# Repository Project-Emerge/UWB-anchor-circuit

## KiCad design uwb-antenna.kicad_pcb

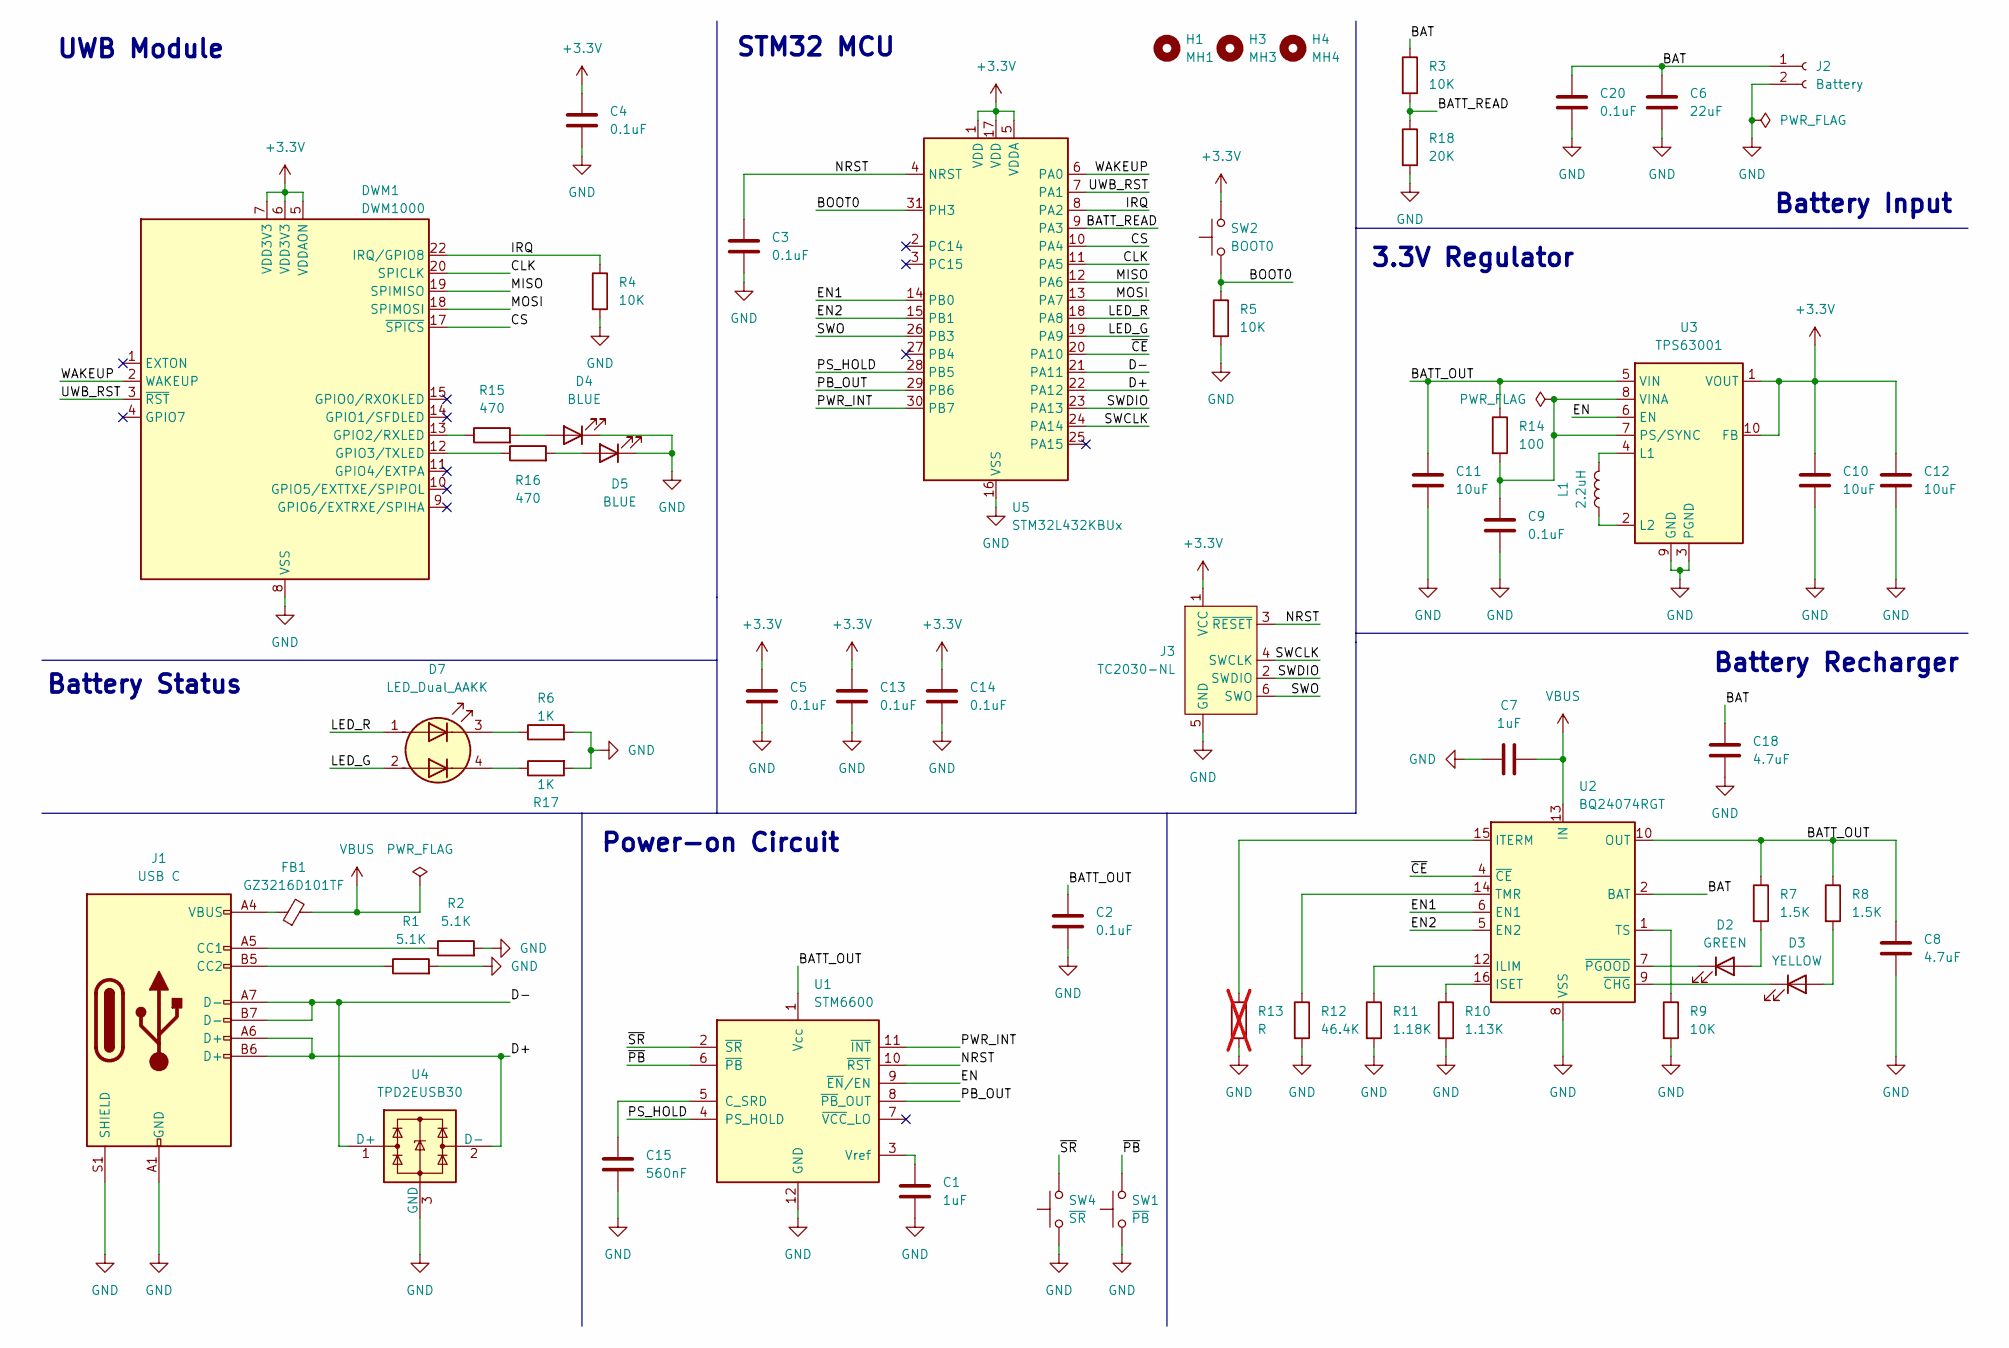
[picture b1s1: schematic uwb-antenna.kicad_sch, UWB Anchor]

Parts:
C1: 1uF; C_0402_1005Metric; LCSC C14445
C2, C3, C4, C5, C13, C14: 0.1uF; C_0402_1005Metric; LCSC C307331
C6: 22uF; C_1210_3225Metric; LCSC C5341638
C7: 1uF; C_0805_2012Metric; LCSC C91185
C8, C18: 4.7uF; C_0805_2012Metric; LCSC C1779
C9: 0.1uF; C_0201_0603Metric; LCSC C14663
C10, C11, C12: 10uF; C_0603_1608Metric; LCSC C48579272
C15: 560nF; C_0402_1005Metric; LCSC C162174
C20: 0.1uF; C_0805_2012Metric; LCSC C49678
D2: GREEN; LED_0402_1005Metric; LCSC C130723
D3: YELLOW; LED_0402_1005Metric; LCSC C136118
D4, D5: BLUE; LED_0402_1005Metric; LCSC C130724
D7: LED_Dual_AAKK; LED_LiteOn_LTST-C295K_1.6x0.8mm; LCSC C284909
DWM1: DWM1000
FB1: GZ3216D101TF; L_1206_3216Metric; LCSC C369799
H1: MH1; MountingHole_3.2mm_M3_Pad
H3: MH3; MountingHole_3.2mm_M3_Pad
H4: MH4; MountingHole_3.2mm_M3_Pad
J1: USB C; USB_C_Receptacle_XKB_U262-16XN-4BVC11; LCSC C319148
J2: Battery; JST_PH_S2B-PH-SM4-TB_1x02-1MP_P2.00mm_Horizontal; LCSC C295747
J3: TC2030-NL; Tag-Connect_TC2030-IDC-NL_2x03_P1.27mm_Vertical
L1: 2.2uH; L_Coilcraft_LPS3010; LCSC C5350399
R1, R2: 5.1K; R_0402_1005Metric; LCSC C25905
R3, R4, R5, R9: 10K; R_0402_1005Metric; LCSC C25744
R6, R17: 1K; R_0402_1005Metric; LCSC C11702
R7, R8: 1.5K; R_0402_1005Metric; LCSC C25867
R10: 1.13K; R_0402_1005Metric; LCSC C67014
R11: 1.18K; R_0402_1005Metric; LCSC C270651
R12: 46.4K; R_0402_1005Metric; LCSC C52378
R13: R; R_0402_1005Metric; not fitted
R14: 100; R_0201_0603Metric; LCSC C22775
R15, R16: 470; R_0402_1005Metric; LCSC C25117
R18: 20K; R_0402_1005Metric; LCSC C25765
SW1: ~{PB}; SW_SPST_B3U-1000P; LCSC C231329
SW2: BOOT0; SW_SPST_B3U-1000P; LCSC C231329
SW4: ~{SR}; SW_SPST_B3U-1000P; LCSC C231329
U1: STM6600; TDFN-12_2x3mm_P0.5mm; LCSC C443976
U2: BQ24074RGT; VQFN-16-1EP_3x3mm_P0.5mm_EP1.6x1.6mm; LCSC1 C54313
U3: TPS63001; Texas_DRC0010J_ThermalVias; LCSC C28060
U4: TPD2EUSB30; Texas_DRT-3; LCSC C97502
U5: STM32L432KBUx; QFN-32-1EP_5x5mm_P0.5mm_EP3.45x3.45mm; LCSC C94784

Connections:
+3.3V: C4.1, C5.1, C10.1, C12.1, C13.1, C14.1, DWM1.5 (VDDAON), DWM1.6 (VDD3V3), DWM1.7 (VDD3V3), J3.1 (VCC), SW2.2, U3.1 (VOUT), U3.10 (FB), U5.1 (VDD), U5.5 (VDDA), U5.17 (VDD)
/BAT: C6.1, C18.1, C20.1, J2.1, R3.1, U2.2 (BAT), U2.3 (BAT)
/BATT_OUT: C2.1, C8.1, C11.1, R7.1, R8.1, R14.1, U1.1 (Vcc), U2.10 (OUT), U2.11 (OUT), U3.5 (VIN)
/BATT_READ: R3.2, R18.1, U5.9 (PA3)
/BOOT0: R5.1, SW2.1, U5.31 (PH3)
/CLK: DWM1.20 (SPICLK), U5.11 (PA5)
/CS: DWM1.17 (~SPICS), U5.10 (PA4)
/D+: J1.A6 (D+), J1.B6 (D+), U4.2 (D-), U5.22 (PA12)
/D-: J1.A7 (D-), J1.B7 (D-), U4.1 (D+), U5.21 (PA11)
/EN: U1.9 (~EN/EN), U3.6 (EN)
/EN1: U2.6 (EN1), U5.14 (PB0)
/EN2: U2.5 (EN2), U5.15 (PB1)
/IRQ: DWM1.22 (IRQ/GPIO8), R4.1, U5.8 (PA2)
/LED_G: D7.2 (A2), U5.19 (PA9)
/LED_R: D7.1 (A1), U5.18 (PA8)
/MISO: DWM1.19 (SPIMISO), U5.12 (PA6)
/MOSI: DWM1.18 (SPIMOSI), U5.13 (PA7)
/NRST: C3.1, J3.3 (~RESET), U1.10 (~RST), U5.4 (NRST)
/PB_OUT: U1.8 (~PB_OUT), U5.29 (PB6)
/PS_HOLD: U1.4 (PS_HOLD), U5.28 (PB5)
/PWR_INT: U1.11 (~INT), U5.30 (PB7)
/SWCLK: J3.4 (SWCLK), U5.24 (PA14)
/SWDIO: J3.2 (SWDIO), U5.23 (PA13)
/SWO: J3.6 (SWO), U5.26 (PB3)
/UWB_RST: DWM1.3 (~RST), U5.7 (PA1)
/WAKEUP: DWM1.2 (WAKEUP), U5.6 (PA0)
/~CE: U2.4 (~CE), U5.20 (PA10)
/~PB: SW1.2, U1.6 (~PB)
/~SR: SW4.2, U1.2 (~SR)
GND: C1.2, C2.2, C3.2, C4.2, C5.2, C6.2, C7.2, C8.2, C9.2, C10.2, C11.2, C12.2, C13.2, C14.2, C15.2, C18.2, C20.2, D4.1 (K), D5.1 (K), DWM1.8 (VSS), DWM1.16 (VSS), DWM1.21 (VSS), DWM1.23 (VSS), DWM1.24 (VSS), J1.A1 (GND), J1.A12 (GND), J1.B1 (GND), J1.B12 (GND), J1.S1 (SHIELD), J2.2, J3.5 (GND), R1.2, R2.2, R4.2, R5.2, R6.2, R9.2, R10.2, R11.2, R12.2, R13.2, R17.2, R18.2, SW1.1, SW4.1, U1.12 (GND), U2.8 (VSS), U2.17 (VSS), U3.3 (PGND), U3.9 (GND), U3.11 (PGND), U4.3 (GND), U5.16 (VSS), U5.32 (VSS), U5.33 (VSS)
unnamed: D2.2 (A), R7.2
unnamed: D2.1 (K), U2.7 (~PGOOD)
unnamed: D3.2 (A), R8.2
unnamed: D3.1 (K), U2.9 (~CHG)
unnamed: D4.2 (A), R15.2
unnamed: D5.2 (A), R16.2
unnamed: D7.3 (K1), R6.1
unnamed: D7.4 (K2), R17.1
unnamed: DWM1.13 (GPIO2/RXLED), R15.1
unnamed: DWM1.12 (GPIO3/TXLED), R16.1
unnamed: FB1.1, J1.A4 (VBUS), J1.A9 (VBUS), J1.B4 (VBUS), J1.B9 (VBUS)
unnamed: J1.A5 (CC1), R2.1
unnamed: J1.B5 (CC2), R1.1
unnamed: C15.1, U1.5 (C_SRD)
unnamed: C1.1, U1.3 (Vref)
unnamed: R11.1, U2.12 (ILIM)
unnamed: R10.1, U2.16 (ISET)
unnamed: R13.1, U2.15 (ITERM)
unnamed: R12.1, U2.14 (TMR)
unnamed: R9.1, U2.1 (TS)
unnamed: L1.2, U3.4 (L1)
unnamed: L1.1, U3.2 (L2)
unnamed: C9.1, R14.2, U3.7 (PS/SYNC), U3.8 (VINA)
VBUS: C7.1, FB1.2, U2.13 (IN)

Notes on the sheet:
3.3V Regulator
Battery Recharger
Power-on Circuit
STM32 MCU
Battery Status
Battery Input
UWB Module

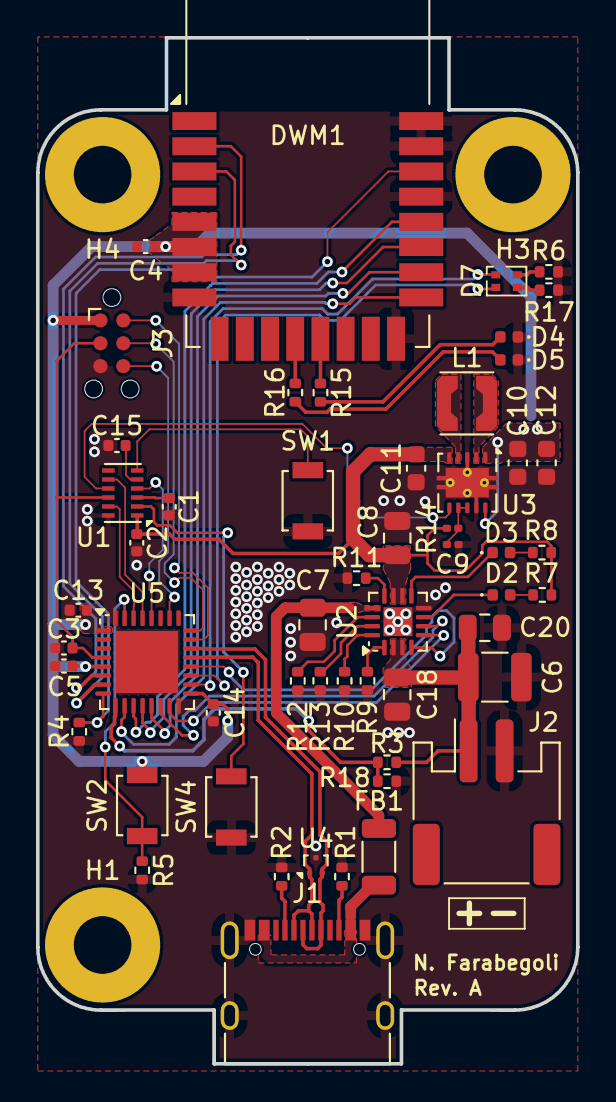
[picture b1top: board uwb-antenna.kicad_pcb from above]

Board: 2 copper layers, 30.0 x 57.0 mm, 57 parts (0 on the bottom side), 54 nets.

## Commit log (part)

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2025-09-12 ci: setup release workflow
2025-09-12 chore: exclude lock files
2025-09-12 feat: initial schematic
2025-09-12 feat: add battery charger
2025-09-13 chore(deps): add renovate.json
2025-09-14 feat: complete schematic
2025-09-14 start placing some components in PCB design
2025-09-15 ci: fix filename
2025-09-15 feat: place other components in the PCB
2025-09-15 add battery filled zone
2025-09-15 add some traces
2025-09-17 update PCB outline
2025-09-17 complete PCB design
2025-09-17 add connector 3d model
2025-09-18 Add Mergify configuration file
2025-09-18 minors on PCB
2025-09-18 add panelized version
2025-09-18 feat: minors in traces and routing
2025-09-18 feat: add panelized version
2025-09-19 chore(deps): update dependency @semantic-release/github to v10
2025-09-20 chore(deps): update dependency @semantic-release/github to v10 (#2)
2025-09-20 chore(deps): update dependency @semantic-release/github to v11
2025-09-20 chore(deps): update dependency @semantic-release/github to v11 (#3)
2025-09-20 chore(deps): update dependency semantic-release to v23
2025-09-20 chore(deps): update dependency semantic-release to v23 (#4)
2025-09-20 chore(deps): update dependency semantic-release to v24
2025-09-20 chore(deps): update dependency semantic-release to v24 (#5)
2025-09-20 ci(deps): update actions/checkout action to v5
2025-09-20 ci(deps): update actions/checkout action to v5 (#6)
2025-09-20 ci(deps): update actions/download-artifact action to v5
2025-09-20 ci(deps): update softprops/action-gh-release action to v2
2025-09-20 ci(deps): update actions/download-artifact action to v5 (#7)
2025-09-21 ci(deps): update softprops/action-gh-release action to v2 (#8)
2025-09-23 ci: release also .step file
2025-10-18 chore(deps): update dependency @semantic-release/github to v12
2025-10-18 chore(deps): update dependency @semantic-release/github to v12 (#10)
2025-10-18 chore(deps): update dependency semantic-release to v25
2025-10-19 chore(deps): update dependency semantic-release to v25 (#11)
2025-10-25 ci(deps): update actions/download-artifact action to v6
2025-10-25 ci(deps): update actions/download-artifact action to v6 (#12)
2025-10-25 ci(deps): update actions/upload-artifact action to v5
2025-10-25 ci(deps): update actions/upload-artifact action to v5 (#13)
2025-11-20 ci(deps): update actions/checkout action to v6
2025-11-20 ci(deps): update actions/checkout action to v6 (#14)
2025-12-12 ci(deps): update actions/download-artifact action to v7
2025-12-13 ci(deps): update actions/download-artifact action to v7 (#15)
2025-12-13 ci(deps): update actions/upload-artifact action to v6
2025-12-13 ci(deps): update actions/upload-artifact action to v6 (#16)
2026-02-26 ci(deps): update actions/download-artifact action to v8
2026-02-27 ci(deps): update actions/download-artifact action to v8 (#17)
2026-02-27 ci(deps): update actions/upload-artifact action to v7
2026-02-27 ci(deps): update actions/upload-artifact action to v7 (#18)
2026-04-03 ci(deps): update actions-for-kicad/kicad-actions action to v2
2026-04-04 ci(deps): update actions-for-kicad/kicad-actions action to v2 (#19)
2026-04-12 ci(deps): update softprops/action-gh-release action to v3
2026-04-12 ci(deps): update softprops/action-gh-release action to v3 (#20)
2026-06-18 ci(deps): update actions/checkout action to v7
2026-06-18 ci(deps): update actions/checkout action to v7 (#21)
